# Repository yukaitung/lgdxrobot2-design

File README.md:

# LGDXRobot2 Design

## Overview

LGDXRobot2 is a Mecanum wheels mobile robot 

This repository contains the controller circuit board design and the robot’s CAD files. It also provides export files for manufacturing the parts without the need to install any software.

* LGDXRobot2 Design: ([GitLab](https://gitlab.com/lgdxrobotics/lgdxrobot2-design) | [GitHub](https://github.com/yukaitung/lgdxrobot2-design))
* LGDXRobot2 MCU: ([GitLab](https://gitlab.com/lgdxrobotics/lgdxrobot2-mcu) | [GitHub](https://github.com/yukaitung/lgdxrobot2-mcu))
* LGDXRobot2 ChassisTuner: ([GitLab](https://gitlab.com/lgdxrobotics/lgdxrobot2-chassistuner) | [GitHub](https://github.com/yukaitung/lgdxrobot2-chassistuner))
* LGDXRobot2 ROS 2: ([GitLab](https://gitlab.com/lgdxrobotics/lgdxrobot2-ros2) | [GitHub](https://github.com/yukaitung/lgdxrobot2-ros2))

### Getting Help

* [Homepage](https://lgdxrobot.uk/lgdxrobot2/)
* [Documentation](https://lgdxrobot.uk/lgdxrobot2/docs/)
* Issue boards on both GitLab and GitHub

## Getting Started

### Chassis

The `Chassis` folder contains the CAD files for the robot. These files require FreeCAD to open. The exported files are located in the `Chassis/Exports` folder.

The root `Chassis` folder includes the designs for all plates and a demo assembly in the `Assembly.FCStd` file. The `Chassis/Components` folder contains CAD files for other parts, which are provided for illustration purposes only.

To manufacture the chassis, you can submit the files in the `Chassis/Exports` folder to a laser cutting service.

### Contorller Board

The `Board` folder contains the design files for the controller board. The board is designed using KiCad, and the exported files are located in the `Board/Exports` folder.

To manufacture the board, simply zip the contents of the `Board/Exports` folder and send it to a PCB manufacturer.

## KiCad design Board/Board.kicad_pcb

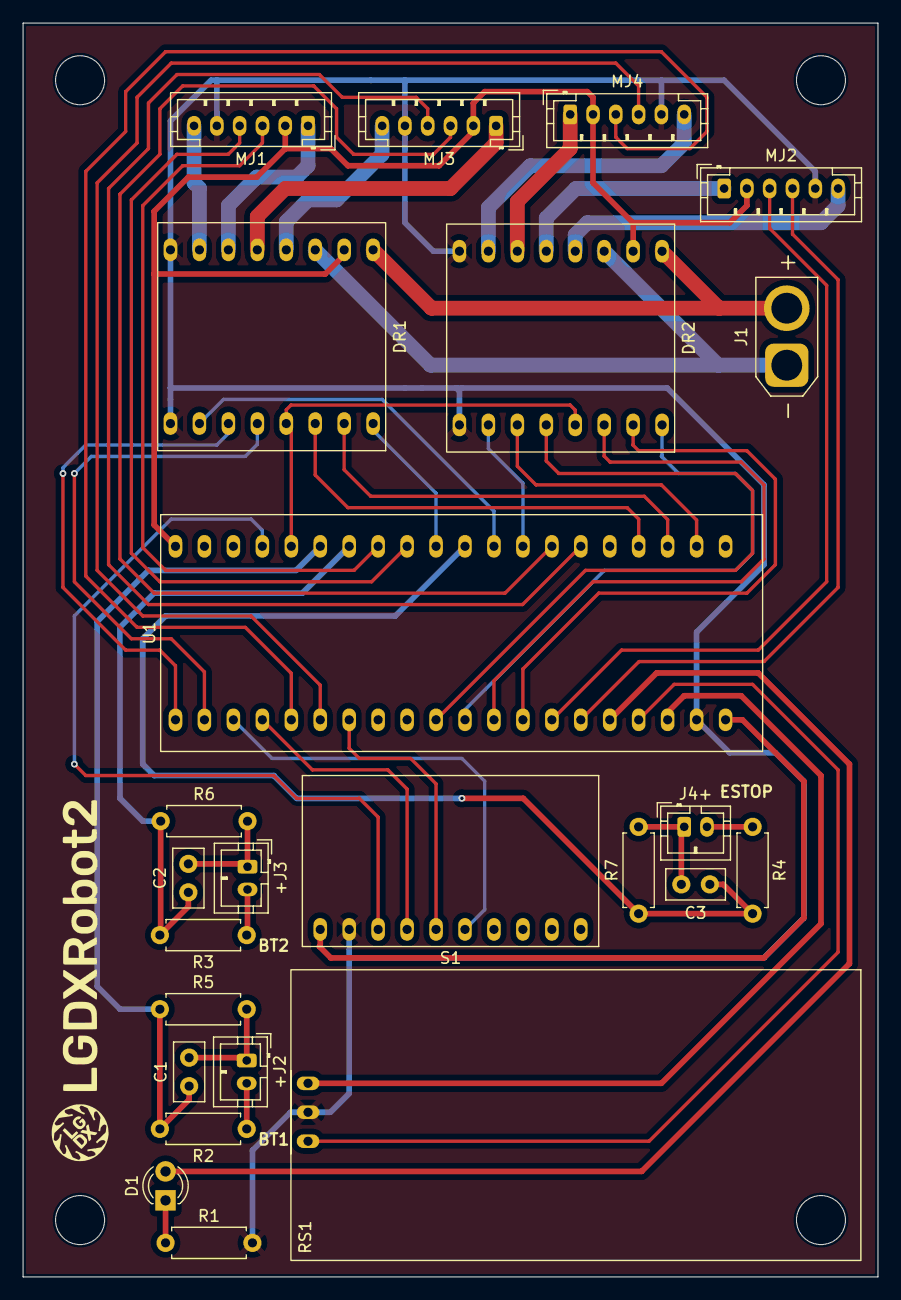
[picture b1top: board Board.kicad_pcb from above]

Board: 2 copper layers, 75.0 x 110.0 mm, 24 parts (0 on the bottom side), 51 nets.

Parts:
+J2, +J3: PH2.0 2P; JST_PH_B2B-PH-K_1x02_P2.00mm_Vertical
C1, C2, C3: 0.1uF; C_Disc_D5.0mm_W2.5mm_P2.50mm
D1: RED_LED; LED_D3.0mm
DR1, DR2: TB6612FNG
J1: XT30 Female; AMASS_XT30U-F_1x02_P5.0mm_Vertical
J4+: PH2.0 2P; JST_PH_B2B-PH-K_1x02_P2.00mm_Vertical
MJ1, MJ2, MJ3, MJ4: JST_PH_B6B-PH-K_1x06_P2.00mm_Vertical
R1: 220R; R_Axial_DIN0207_L6.3mm_D2.5mm_P7.62mm_Horizontal
R2, R3, R4: 68k; R_Axial_DIN0207_L6.3mm_D2.5mm_P7.62mm_Horizontal
R5, R6, R7: 10k; R_Axial_DIN0207_L6.3mm_D2.5mm_P7.62mm_Horizontal
RS1: Relay
S1: ICM20948
U1: BlackPill

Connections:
+12V: DR1.24 (VM1), DR2.24 (VM1), J1.2
/3V348: S1.1 (VCC), U1.48 (3V3)
/5V98: DR1.20 (VCC), DR2.20 (VCC), MJ1.2 (ENC_VCC), MJ2.2 (ENC_VCC), MJ3.2 (ENC_VCC), MJ4.2 (ENC_VCC), U1.98 (5V)
/5V99: RS1.1 (VCC), U1.99 (5V)
/GND47: DR1.18 (GND), DR2.18 (GND), MJ1.5 (ENC_GND), MJ2.5 (ENC_GND), MJ3.5 (ENC_GND), MJ4.5 (ENC_GND), R1.2, RS1.2 (GND), S1.2 (GND), U1.47 (GND)
/PA0_MJ3CH1: MJ3.4 (ENC_CH1), U1.10 (PA0)
/PA1_MJ3CH2: MJ3.3 (ENC_CH2), U1.11 (PA1)
/PA2_DR2PWMB: DR2.15 (PWMB), U1.12 (PA2)
/PA3_DR1PWMB: DR1.15 (PWMB), U1.13 (PA3)
/PA4_ESTOP: C3.1, R4.2, R7.1, U1.14 (PA4)
/PA5_DR1PWMA: DR1.23 (PWMA), U1.15 (PA5)
/PA6_MJ1CH1: MJ1.4 (ENC_CH1), U1.16 (PA6)
/PA7_MJ1CH2: MJ1.3 (ENC_CH2), U1.17 (PA7)
/PA8_MJ4CH2: MJ4.3 (ENC_CH2), U1.29 (PA8)
/PA9_MJ4CH1: MJ4.4 (ENC_CH1), U1.30 (PA9)
/PA10_NCS: S1.5 (NCS), U1.31 (PA10)
/PA15_DR2BIN1: DR2.17 (BIN1), U1.38 (PA15)
/PB0_BT2: C2.1, R3.2, R6.1, U1.18 (PB0)
/PB1_BT1: C1.1, R2.2, R5.1, U1.19 (PB1)
/PB2_DRxSTBY: DR1.19 (STBY), DR2.19 (STBY), U1.20 (PB2)
/PB3_DR2PWMA: DR2.23 (PWMA), U1.39 (PB3)
/PB4_DR2AIN1: DR2.21 (AIN1), U1.40 (PB4)
/PB5_DR2AIN2: DR2.22 (AIN2), U1.41 (PB5)
/PB6_MJ2CH2: MJ2.3 (ENC_CH2), U1.42 (PB6)
/PB7_MJ2CH1: MJ2.4 (ENC_CH1), U1.43 (PB7)
/PB8_D1: D1.2 (A), U1.45 (PB8)
/PB9_RS1: RS1.3 (INPUT), U1.46 (PB9)
/PB10_SCLK: S1.3 (SCLK), U1.21 (PB10)
/PB12_DR1BIN2: DR1.16 (BIN2), U1.25 (PB12)
/PB13_DR1BIN1: DR1.17 (BIN1), U1.26 (PB13)
/PB14_ADO: S1.6 (ADO), U1.27 (PB14)
/PB15_SDA: S1.4 (SDI), U1.28 (PB15)
/PC13_DR2BIN2: DR2.16 (BIN2), U1.2 (PC13)
/PC14_DR1AIN2: DR1.22 (AIN2), U1.3 (PC14)
/PC15_DR1AIN1: DR1.21 (AIN1), U1.4 (PC15)
GND: DR1.3 (PGND1), DR2.3 (PGND1), J1.1
unnamed: D1.1 (K), R1.1
unnamed: +J2.1, C1.2, R5.2
unnamed: +J2.2, R2.1
unnamed: +J3.1, C2.2, R6.2
unnamed: +J3.2, R3.1
unnamed: C3.2, J4+.1, R7.2
unnamed: J4+.2, R4.1
unnamed: DR1.11 (BO1), MJ1.6 (MV+)
unnamed: DR1.7 (BO2), MJ1.1 (MV-)
unnamed: DR2.1 (AO1), MJ2.6 (MV+)
unnamed: DR2.5 (AO2), MJ2.1 (MV-)
unnamed: DR1.1 (AO1), MJ3.6 (MV+)
unnamed: DR1.5 (AO2), MJ3.1 (MV-)
unnamed: DR2.11 (BO1), MJ4.6 (MV+)
unnamed: DR2.7 (BO2), MJ4.1 (MV-)

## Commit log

2025-10-04 init push
2025-10-04 draw circuit
2025-10-04 footprint
2025-10-04 net class
2025-10-05 update board
2025-10-09 new design
2025-10-14 cad bracket
2025-10-15 add components
2025-10-15 LGDX BORAD
2025-10-15 update motor
2025-10-16 wheel
2025-10-16 wheel base
2025-10-16 wheels
2025-10-16 power
2025-10-16 board hole
2025-10-16 bottom plate
2025-10-16 bottom plate update
2025-10-16 pc plate
2025-10-16 all plate
2025-10-16 coupling nuts
2025-10-16 assembly
2025-10-17 update files
2025-10-17 update screw
2025-10-19 Add new file
2025-10-24 Assembly update
2025-10-25 new wheel
2025-10-25 update webots
2025-10-26 cam position
2025-11-06 fix board design
2025-11-11 Edit README.md
2025-12-21 pc plate update
2025-12-21 update top plate
2025-12-21 update install and output
2025-12-21 update sim assmbely
2026-01-18 update borad 2
2026-01-18 board v2 pcb
2026-01-18 new board
2026-01-19 update logo
2026-04-19 update link
